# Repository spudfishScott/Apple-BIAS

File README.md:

# Apple-BIAS
BIAS SPI Master Card for Apple ][

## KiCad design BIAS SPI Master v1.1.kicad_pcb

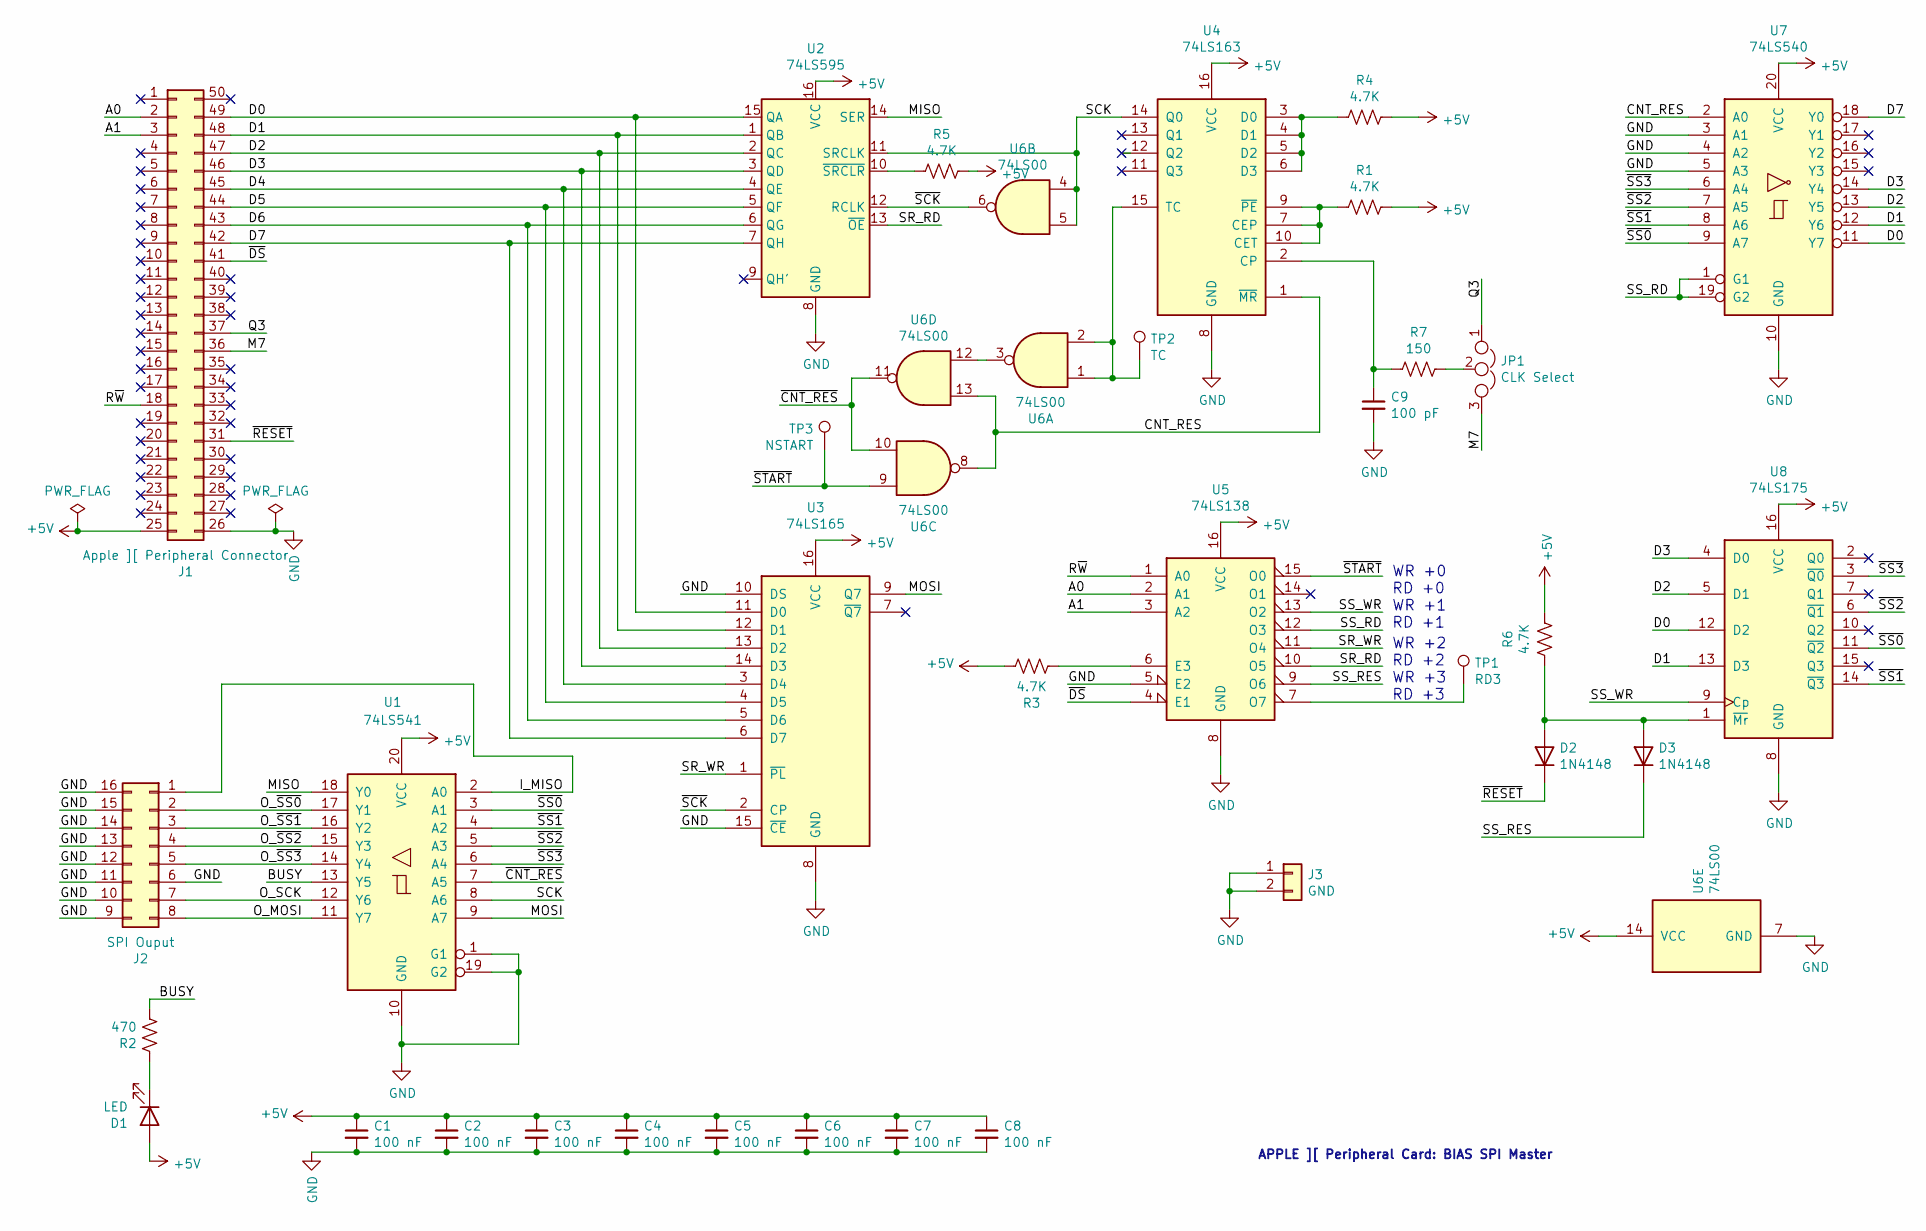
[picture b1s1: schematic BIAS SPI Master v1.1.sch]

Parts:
C1, C2, C3, C4, C5, C6, C7, C8: 100 nF; C_Axial_L3.8mm_D2.6mm_P7.50mm_Horizontal
C9: 100 pF; C_Rect_L7.0mm_W2.0mm_P5.00mm
D1: LED; LED_D3.0mm_Horizontal_O1.27mm_Z2.0mm
D2, D3: 1N4148; D_DO-35_SOD27_P7.62mm_Horizontal
J1: Apple ][ Peripheral Connector; Male_Card-Edge_50_pin__100_mil
J2: SPI Ouput; DIP-16_W7.62mm_Socket_LongPads
J3: GND; PinHeader_1x02_P2.54mm_Vertical
JP1: CLK Select; PinHeader_1x03_P2.54mm_Vertical
R1, R3, R4, R5, R6: 4.7K; R_Axial_DIN0207_L6.3mm_D2.5mm_P10.16mm_Horizontal
R2: 470; R_Axial_DIN0207_L6.3mm_D2.5mm_P10.16mm_Horizontal
R7: 150; R_Axial_DIN0207_L6.3mm_D2.5mm_P10.16mm_Horizontal
TP1: RD3; PinHeader_1x01_P2.54mm_Vertical
TP2: TC; PinHeader_1x01_P2.54mm_Vertical
TP3: NSTART; PinHeader_1x01_P2.54mm_Vertical
U1: 74LS541; DIP-20_W7.62mm_Socket_LongPads
U2: 74LS595; DIP-16_W7.62mm_Socket_LongPads
U3: 74LS165; DIP-16_W7.62mm_Socket_LongPads
U4: 74LS163; DIP-16_W7.62mm_Socket_LongPads
U5: 74LS138; DIP-16_W7.62mm_Socket_LongPads
U6: 74LS00; DIP-14_W7.62mm_Socket_LongPads
U7: 74LS540; DIP-20_W7.62mm_Socket_LongPads
U8: 74LS175; DIP-16_W7.62mm_Socket_LongPads

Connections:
+5V: C1.1, C2.1, C3.1, C4.1, C5.1, C6.1, C7.1, C8.1, D1.2 (A), J1.25, R1.1, R3.1, R4.1, R5.1, R6.1, U1.20 (VCC), U2.16 (VCC), U3.16 (VCC), U4.16 (VCC), U5.16 (VCC), U6.14 (VCC), U7.20 (VCC), U8.16 (VCC)
/A0: J1.2, U5.2 (A1)
/A1: J1.3, U5.3 (A2)
/BUSY: R2.2, U1.13 (Y5)
/CNT_RES: U4.1 (~MR), U6.8, U6.13, U7.2 (A0)
/D0: J1.49, U2.15 (QA), U3.11 (D0), U7.11 (Y7), U8.12 (D2)
/D1: J1.48, U2.1 (QB), U3.12 (D1), U7.12 (Y6), U8.13 (D3)
/D2: J1.47, U2.2 (QC), U3.13 (D2), U7.13 (Y5), U8.5 (D1)
/D3: J1.46, U2.3 (QD), U3.14 (D3), U7.14 (Y4), U8.4 (D0)
/D4: J1.45, U2.4 (QE), U3.3 (D4)
/D5: J1.44, U2.5 (QF), U3.4 (D5)
/D6: J1.43, U2.6 (QG), U3.5 (D6)
/D7: J1.42, U2.7 (QH), U3.6 (D7), U7.18 (Y0)
/I_MISO: J2.1, U1.2 (A0)
/M7: J1.36, JP1.3
/MISO: U1.18 (Y0), U2.14 (SER)
/MOSI: U1.9 (A7), U3.9 (Q7)
/O_MOSI: J2.8, U1.11 (Y7)
/O_SCK: J2.7, U1.12 (Y6)
/O_~SS0: J2.2, U1.17 (Y1)
/O_~SS1: J2.3, U1.16 (Y2)
/O_~SS2: J2.4, U1.15 (Y3)
/O_~SS3: J2.5, U1.14 (Y4)
/Q3: J1.37, JP1.1
/R~W: J1.18, U5.1 (A0)
/SCK: U1.8 (A6), U2.11 (SRCLK), U4.14 (Q0), U6.4, U6.5
/SR_RD: U2.13 (~OE), U5.10 (O5)
/SR_WR: U3.1 (~PL), U5.11 (O4)
/SS_RD: U5.12 (O3), U7.1 (G1), U7.19 (G2)
/SS_RES: D3.1 (K), U5.9 (O6)
/SS_WR: U5.13 (O2), U8.9 (Cp)
/~CNT_RES: U1.7 (A5), U6.10, U6.11
/~DS: J1.41, U5.4 (E1)
/~RESET: D2.1 (K), J1.31
/~SCK: U2.12 (RCLK), U3.2 (CP), U6.6
/~SS0: U1.3 (A1), U7.9 (A7), U8.11 (~Q2)
/~SS1: U1.4 (A2), U7.8 (A6), U8.14 (~Q3)
/~SS2: U1.5 (A3), U7.7 (A5), U8.6 (~Q1)
/~SS3: U1.6 (A4), U7.6 (A4), U8.3 (~Q0)
/~START: TP3.1, U5.15 (O0), U6.9
GND: C1.2, C2.2, C3.2, C4.2, C5.2, C6.2, C7.2, C8.2, C9.2, J1.26, J2.6, J2.9, J2.10, J2.11, J2.12, J2.13, J2.14, J2.15, J2.16, J3.1, J3.2, U1.1 (G1), U1.10 (GND), U1.19 (G2), U2.8 (GND), U3.8 (GND), U3.10 (DS), U3.15 (~CE), U4.8 (GND), U5.5 (E2), U5.8 (GND), U6.7 (GND), U7.3 (A1), U7.4 (A2), U7.5 (A3), U7.10 (GND), U8.8 (GND)
unnamed: C9.1, R7.2, U4.2 (CP)
unnamed: D1.1 (K), R2.1
unnamed: D2.2 (A), D3.2 (A), R6.2, U8.1 (~Mr)
unnamed: JP1.2, R7.1
unnamed: R1.2, U4.7 (CEP), U4.9 (~PE), U4.10 (CET)
unnamed: R3.2, U5.6 (E3)
unnamed: R4.2, U4.3 (D0), U4.4 (D1), U4.5 (D2), U4.6 (D3)
unnamed: R5.2, U2.10 (~SRCLR)
unnamed: TP1.1, U5.7 (O7)
unnamed: TP2.1, U4.15 (TC), U6.1, U6.2
unnamed: U6.3, U6.12

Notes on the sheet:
APPLE ][ Peripheral Card: BIAS SPI Master
WR +2 RD +2 WR +3 RD +3
WR +0 RD +0 WR +1 RD +1

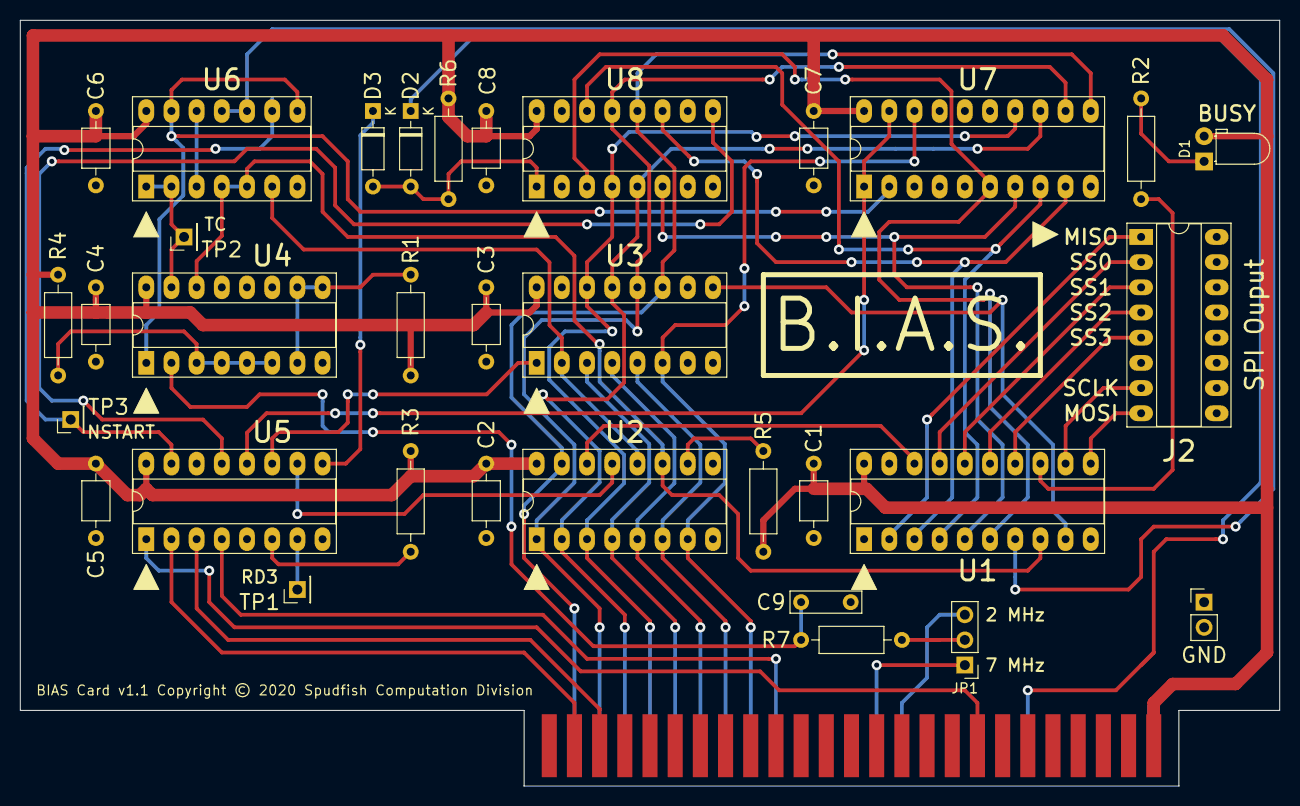
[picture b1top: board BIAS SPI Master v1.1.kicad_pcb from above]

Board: 2 copper layers, 127.0 x 77.2 mm, 34 parts (0 on the bottom side), 52 nets.

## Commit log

2020-01-13 Initial Upload
2020-03-19 fixed a couple of typos
2020-08-06 Added low pass filter to clean up Apple ][ clock signal ringing
2020-08-07 Fixed RC filter schematic and PCB

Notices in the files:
BIAS SPI Master v1.1.kicad_pcb:
BIAS Card v1.1 Copyright © 2020 Spudfish Computation Division
